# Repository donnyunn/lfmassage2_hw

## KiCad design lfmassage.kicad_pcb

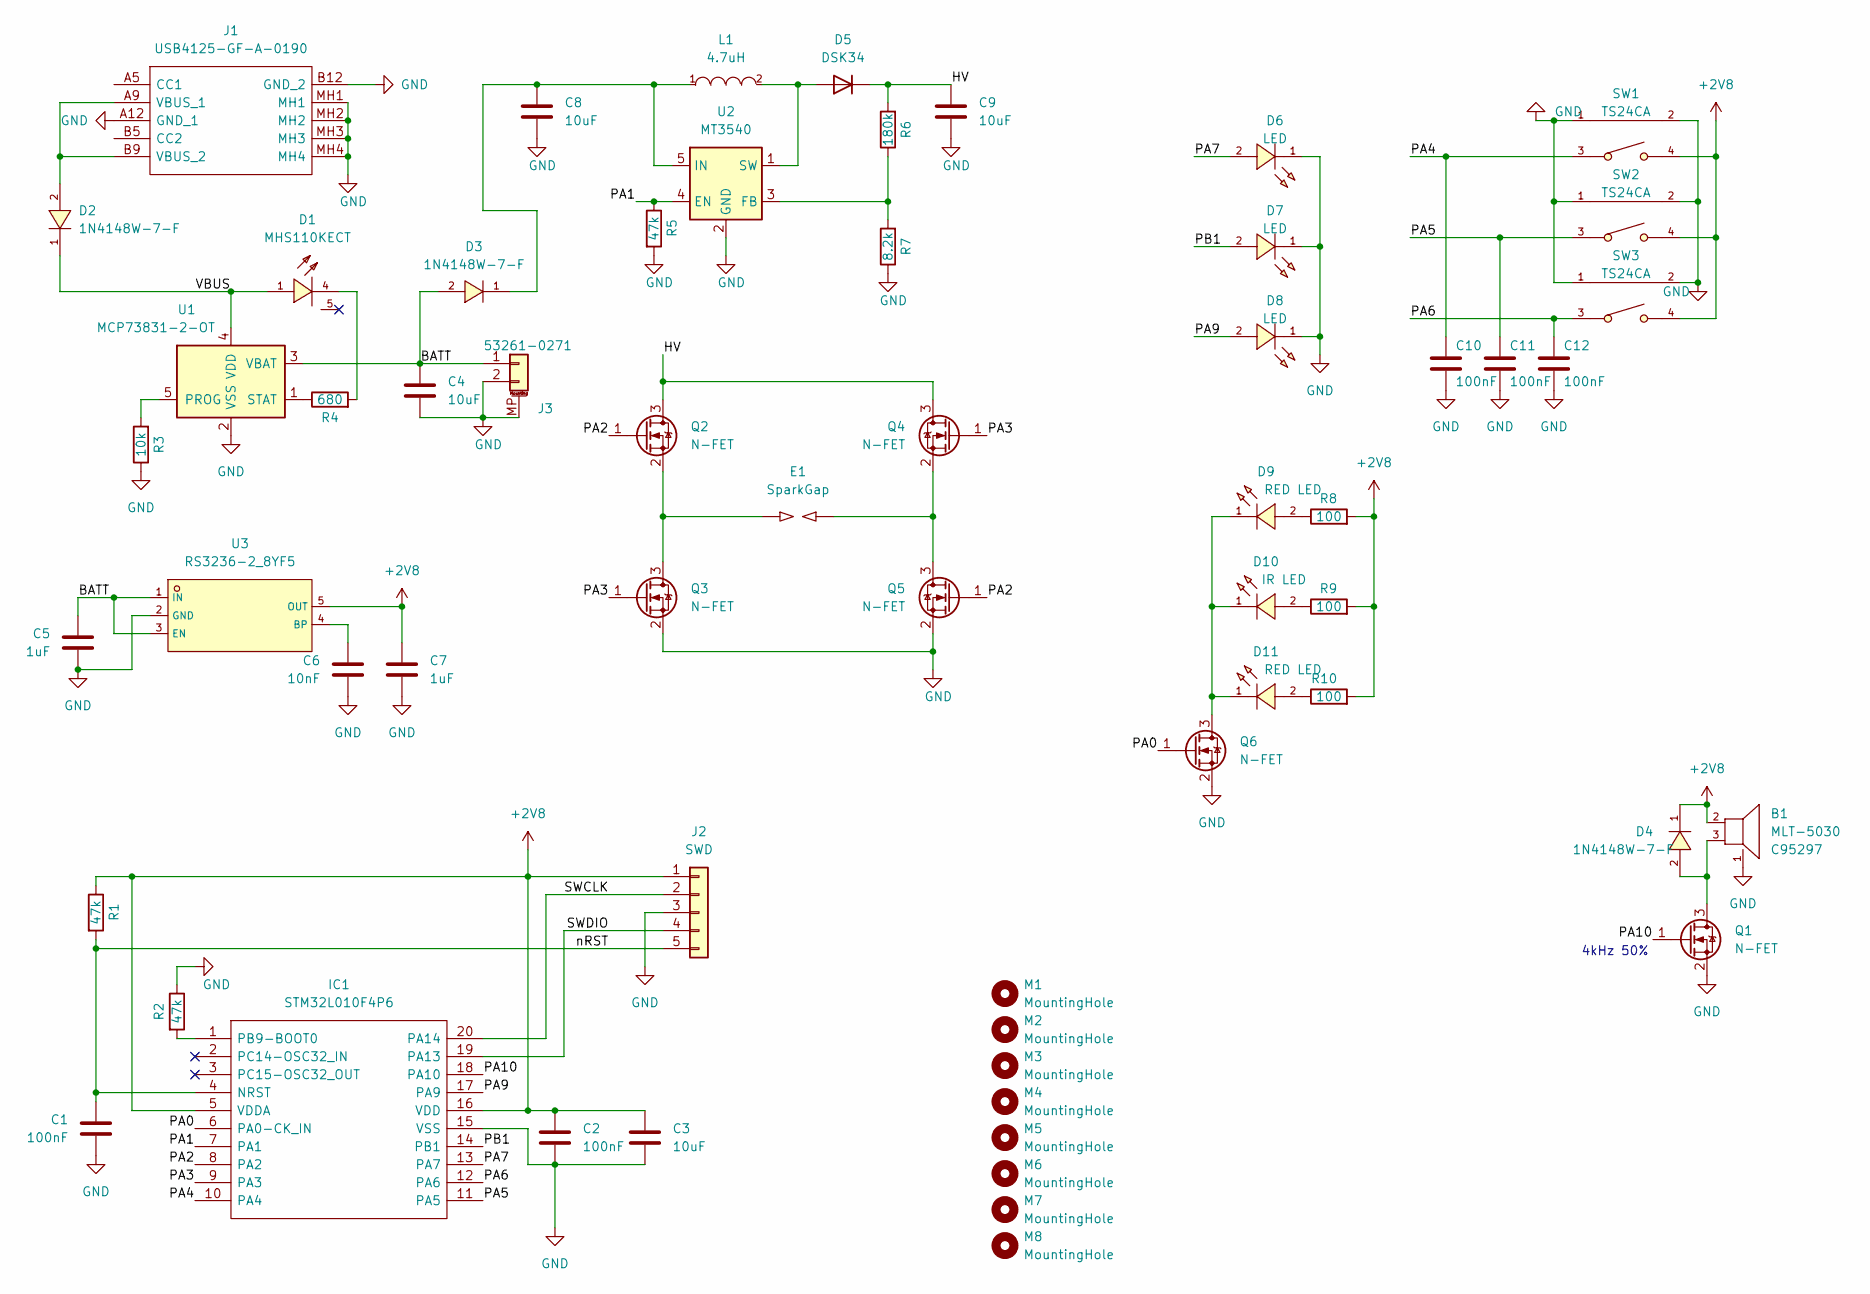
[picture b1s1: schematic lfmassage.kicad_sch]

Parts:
B1: MLT-5030; MPN MLT-5030; LCSC Part C95297
C1, C2, C10, C11, C12: 100nF; C_0402_1005Metric; MPN 0402B104K160NT; LCSC Part C41851
C3, C4, C8: 10uF; C_0603_1608Metric; MPN 0603X106K160NT; LCSC Part C70225
C5, C7: 1uF; C_0402_1005Metric; MPN 0402X105K160CT; LCSC Part C83063
C6: 10nF; C_0402_1005Metric; MPN 0402B103K500NT; LCSC Part C1524
C9: 10uF; C_1206_3216Metric; MPN CL31A106KBHNNNE; LCSC Part C13585
D1: MHS110KECT; LED-ARRAY-SMD_3P-L3.00-W1.50-R-RD; MPN MHS110KECT; LCSC Part C389527
D2, D3, D4: 1N4148W-7-F; SOD-123_L2.7-W1.6-LS3.7-RD-1; MPN 1N4148W-7-F; LCSC Part C83528
D5: DSK34; D_SOD-123; MPN DSK34; LCSC Part C41029
D6, D7, D8: LED; XL-1608UWC-04; MPN XL-1608UWC-04; LCSC Part C965808
D9, D11: RED LED; LED0805-RD; MPN XL-2012SURC; LCSC Part C965812
D10: IR LED; LED0805-RD; MPN XL-2012HIRC-850; LCSC Part C965888
E1: SparkGap; Electrode
IC1: STM32L010F4P6; SOP65P640X120-20N; MPN STM32L010F4P6; LCSC Part C529415
J1: USB4125-GF-A-0190; USB4125GFA0190; MPN HC-TYPE-C-6P-01A; LCSC Part C2894893
J2: SWD; PinHeader_1x05_P2.54mm_Vertical
J3: 53261-0271; Molex_PicoBlade_53261-0271_1x02-1MP_P1.25mm_Horizontal; MPN 532610271; LCSC Part C189700
L1: 4.7uH; L_Bourns-SRN4018; MPN SWPA4030S4R7MT; LCSC Part C57269
M1, M2, M3, M4, M5, M6, M7, M8: MountingHole; MountingHole_2.2mm_M2
Q1, Q2, Q3, Q4, Q5, Q6: N-FET; SOT-23; MPN 2N7002; LCSC Part C8545
R1, R2, R5: 47k; R_0402_1005Metric; MPN 0402WGF4702TCE; LCSC Part C25792
R3: 10k; R_0402_1005Metric; MPN AC0402FR-0710KL; LCSC Part C144807
R4: 680; R_0402_1005Metric; MPN 0402WGF6801TCE; LCSC Part C25917
R6: 180k; R_0402_1005Metric; MPN RC0402FR-07180KL; LCSC Part C138046
R7: 8.2k; R_0402_1005Metric; MPN RTT028201FTH; LCSC Part C103167
R8, R9, R10: 100; R_0402_1005Metric; MPN AC0402FR-07100RL; LCSC Part C144808
SW1: TS24CA; MPN TS24CA; LCSC Part C393942
SW2, SW3: TS24CA; MPN TS24CA; LCSC C393942
U1: MCP73831-2-OT; SOT-23-5; MPN MCP73831T-2ACI/OT; LCSC Part C424093
U2: MT3540; SOT-23-5; MPN MT3540; LCSC Part C181744
U3: RS3236-2_8YF5; SOT-23-5_L2.9-W1.6-P0.95-LS2.8-BL; MPN RS3236-2.8YF5; LCSC Part C379345

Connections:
+2V8: B1.2 (+), C2.1, C3.1, C7.1, D4.1 (C), IC1.5 (VDDA), IC1.16 (VDD), J2.1, R1.1, R8.2, R9.2, R10.2, SW1.4, SW2.4, SW3.4, U3.5 (OUT)
/BATT: C4.1, C5.2, D3.2 (A), J3.1, U1.3 (VBAT), U3.1 (IN), U3.3 (EN)
/HV: C9.1, D5.1 (K), Q2.3 (D), Q4.3 (D), R6.2
/PA0: IC1.6 (PA0-CK_IN), Q6.1 (G)
/PA1: IC1.7 (PA1), R5.1, U2.4 (EN)
/PA2: IC1.8 (PA2), Q2.1 (G), Q5.1 (G)
/PA3: IC1.9 (PA3), Q3.1 (G), Q4.1 (G)
/PA4: C10.1, IC1.10 (PA4), SW1.3
/PA5: C11.1, IC1.11 (PA5), SW2.3
/PA6: C12.1, IC1.12 (PA6), SW3.3
/PA7: D6.2 (A), IC1.13 (PA7)
/PA9: D8.2 (A), IC1.17 (PA9)
/PA10: IC1.18 (PA10), Q1.1 (G)
/PB1: D7.2 (A), IC1.14 (PB1)
/SWCLK: IC1.20 (PA14), J2.2
/SWDIO: IC1.19 (PA13), J2.4
/VBUS: D1.1 (+), D2.1 (C), U1.4 (VDD)
/nRST: C1.2, IC1.4 (NRST), J2.5, R1.2
GND: B1.1 (NC), C1.1, C2.2, C3.2, C4.2, C5.1, C6.1, C7.2, C8.2, C9.2, C10.2, C11.2, C12.2, D6.1 (K), D7.1 (K), D8.1 (K), IC1.15 (VSS), J1.A12 (GND_1), J1.B12 (GND_2), J1.MH1, J1.MH2, J1.MH3, J1.MH4, J2.3, J3.2, J3.MP (MountPin), Q1.2 (S), Q3.2 (S), Q5.2 (S), Q6.2 (S), R2.1, R3.1, R5.2, R7.1, SW1.1, SW1.2, SW2.1, SW2.2, SW3.1, SW3.2, U1.2 (VSS), U2.2 (GND), U3.2 (GND)
unnamed: C8.1, D3.1 (C), L1.1, U2.5 (IN)
unnamed: D1.4 (-), R4.2
unnamed: D9.2 (A), R8.1
unnamed: D9.1 (K), D10.1 (K), D11.1 (K), Q6.3 (D)
unnamed: D10.2 (A), R9.1
unnamed: D11.2 (A), R10.1
unnamed: E1.1, Q2.2 (S), Q3.3 (D)
unnamed: E1.2, Q4.2 (S), Q5.3 (D)
unnamed: D2.2 (A), J1.A9 (VBUS_1), J1.B9 (VBUS_2)
unnamed: D5.2 (A), L1.2, U2.1 (SW)
unnamed: B1.3 (-), D4.2 (A), Q1.3 (D)
unnamed: IC1.1 (PB9-BOOT0), R2.2
unnamed: R6.1, R7.2, U2.3 (FB)
unnamed: R4.1, U1.1 (STAT)
unnamed: R3.2, U1.5 (PROG)
unnamed: C6.2, U3.4 (BP)

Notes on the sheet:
4kHz 50%

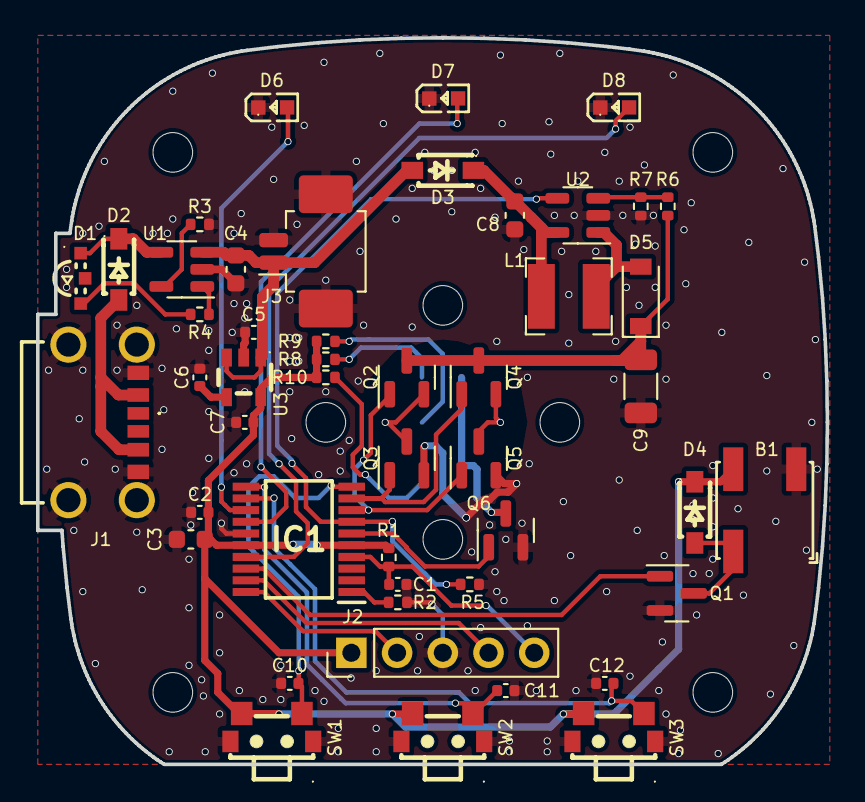
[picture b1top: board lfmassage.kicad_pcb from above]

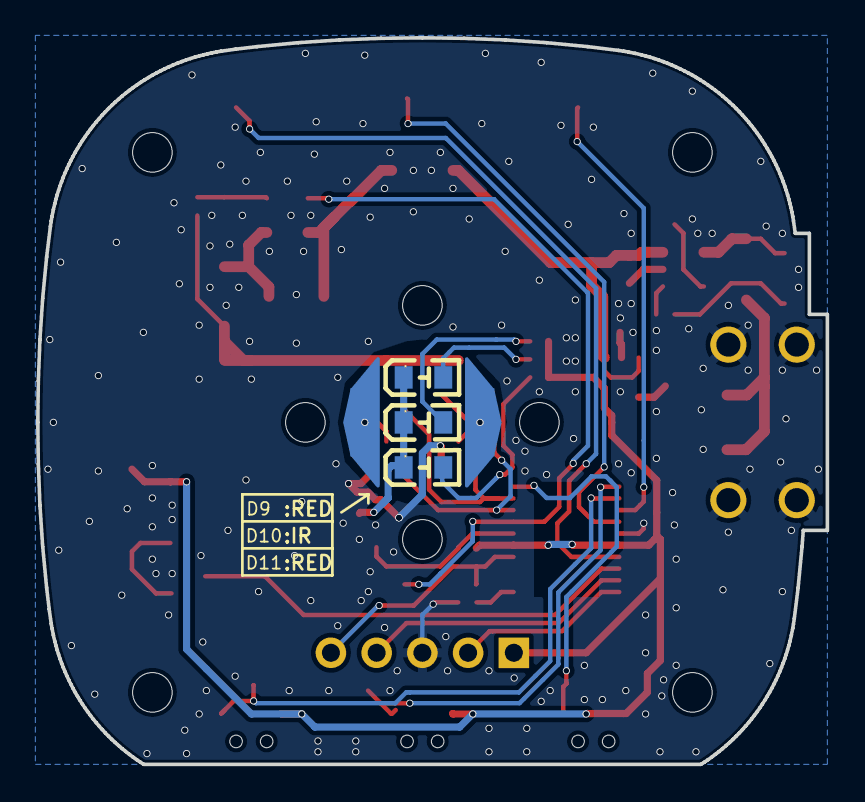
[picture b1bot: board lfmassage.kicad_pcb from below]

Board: 2 copper layers, 43.9 x 40.4 mm, 60 parts (4 on the bottom side), 35 nets.

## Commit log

2022-07-01 init project
2022-07-01 2022-07-01
2022-07-11 2022-07-11
2022-07-11 2022-07-11 2
2022-07-25 MCU change to STM32L031F6P6
